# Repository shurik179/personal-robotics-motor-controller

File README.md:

# Personal Robotics Motor Controller

This repository contain design files for a 2-channel motor
controller board, designed by members of Personal Robotics discord server.

The controller is based on [DRV8874](https://www.ti.com/lit/ds/symlink/drv8874.pdf) motor driver ICs by TI. The  key
features of this controller are listed below:

* Support for 2 brushed DC motors, 5-24v

* Current limit per channel: 4.5A continuous (with heatsinks), current limited

* Overcurrent, undervoltage, and overtemperature protection

* Support for quadrature encoders for each motor (3.3v)

* An on-board MCU (RP2040) for reading encoder input and
  providing variety of close loop motor control modes

* Serial interface for control by a microcontroller or single board computer

This repository contains both board design files (as KiCad 6.0 project) and
firmware (written using Arduino IDE with Earl Philhower arduino-pico core for RP2040).

Detailed project information is available http://motor-controller.rtfd.io/

## Copyright

This project was started in 2021  by:

* Ichiro Furusato  (https://github.com/ifurusato)

* Adam Green (https://github.com/adamgreen/)

* shurik179 (https://github.com/shurik179)

It is released under Apache license; see file LICENSE for details.

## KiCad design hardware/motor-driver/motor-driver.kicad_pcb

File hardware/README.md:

# Hardware

This directory contains:

* Board design files (in KiCad 6.0 format)

* Bill of Materials (BOM)

The board specs are:

* Dimensions: 60x50 mm

* Stackup: 4-layer, 1.6mm thickness, 1oz copper thickness (outzide layers)

* Mounting holes: 4 holes for M3 screws, in the shape of rectangle 43x53mm

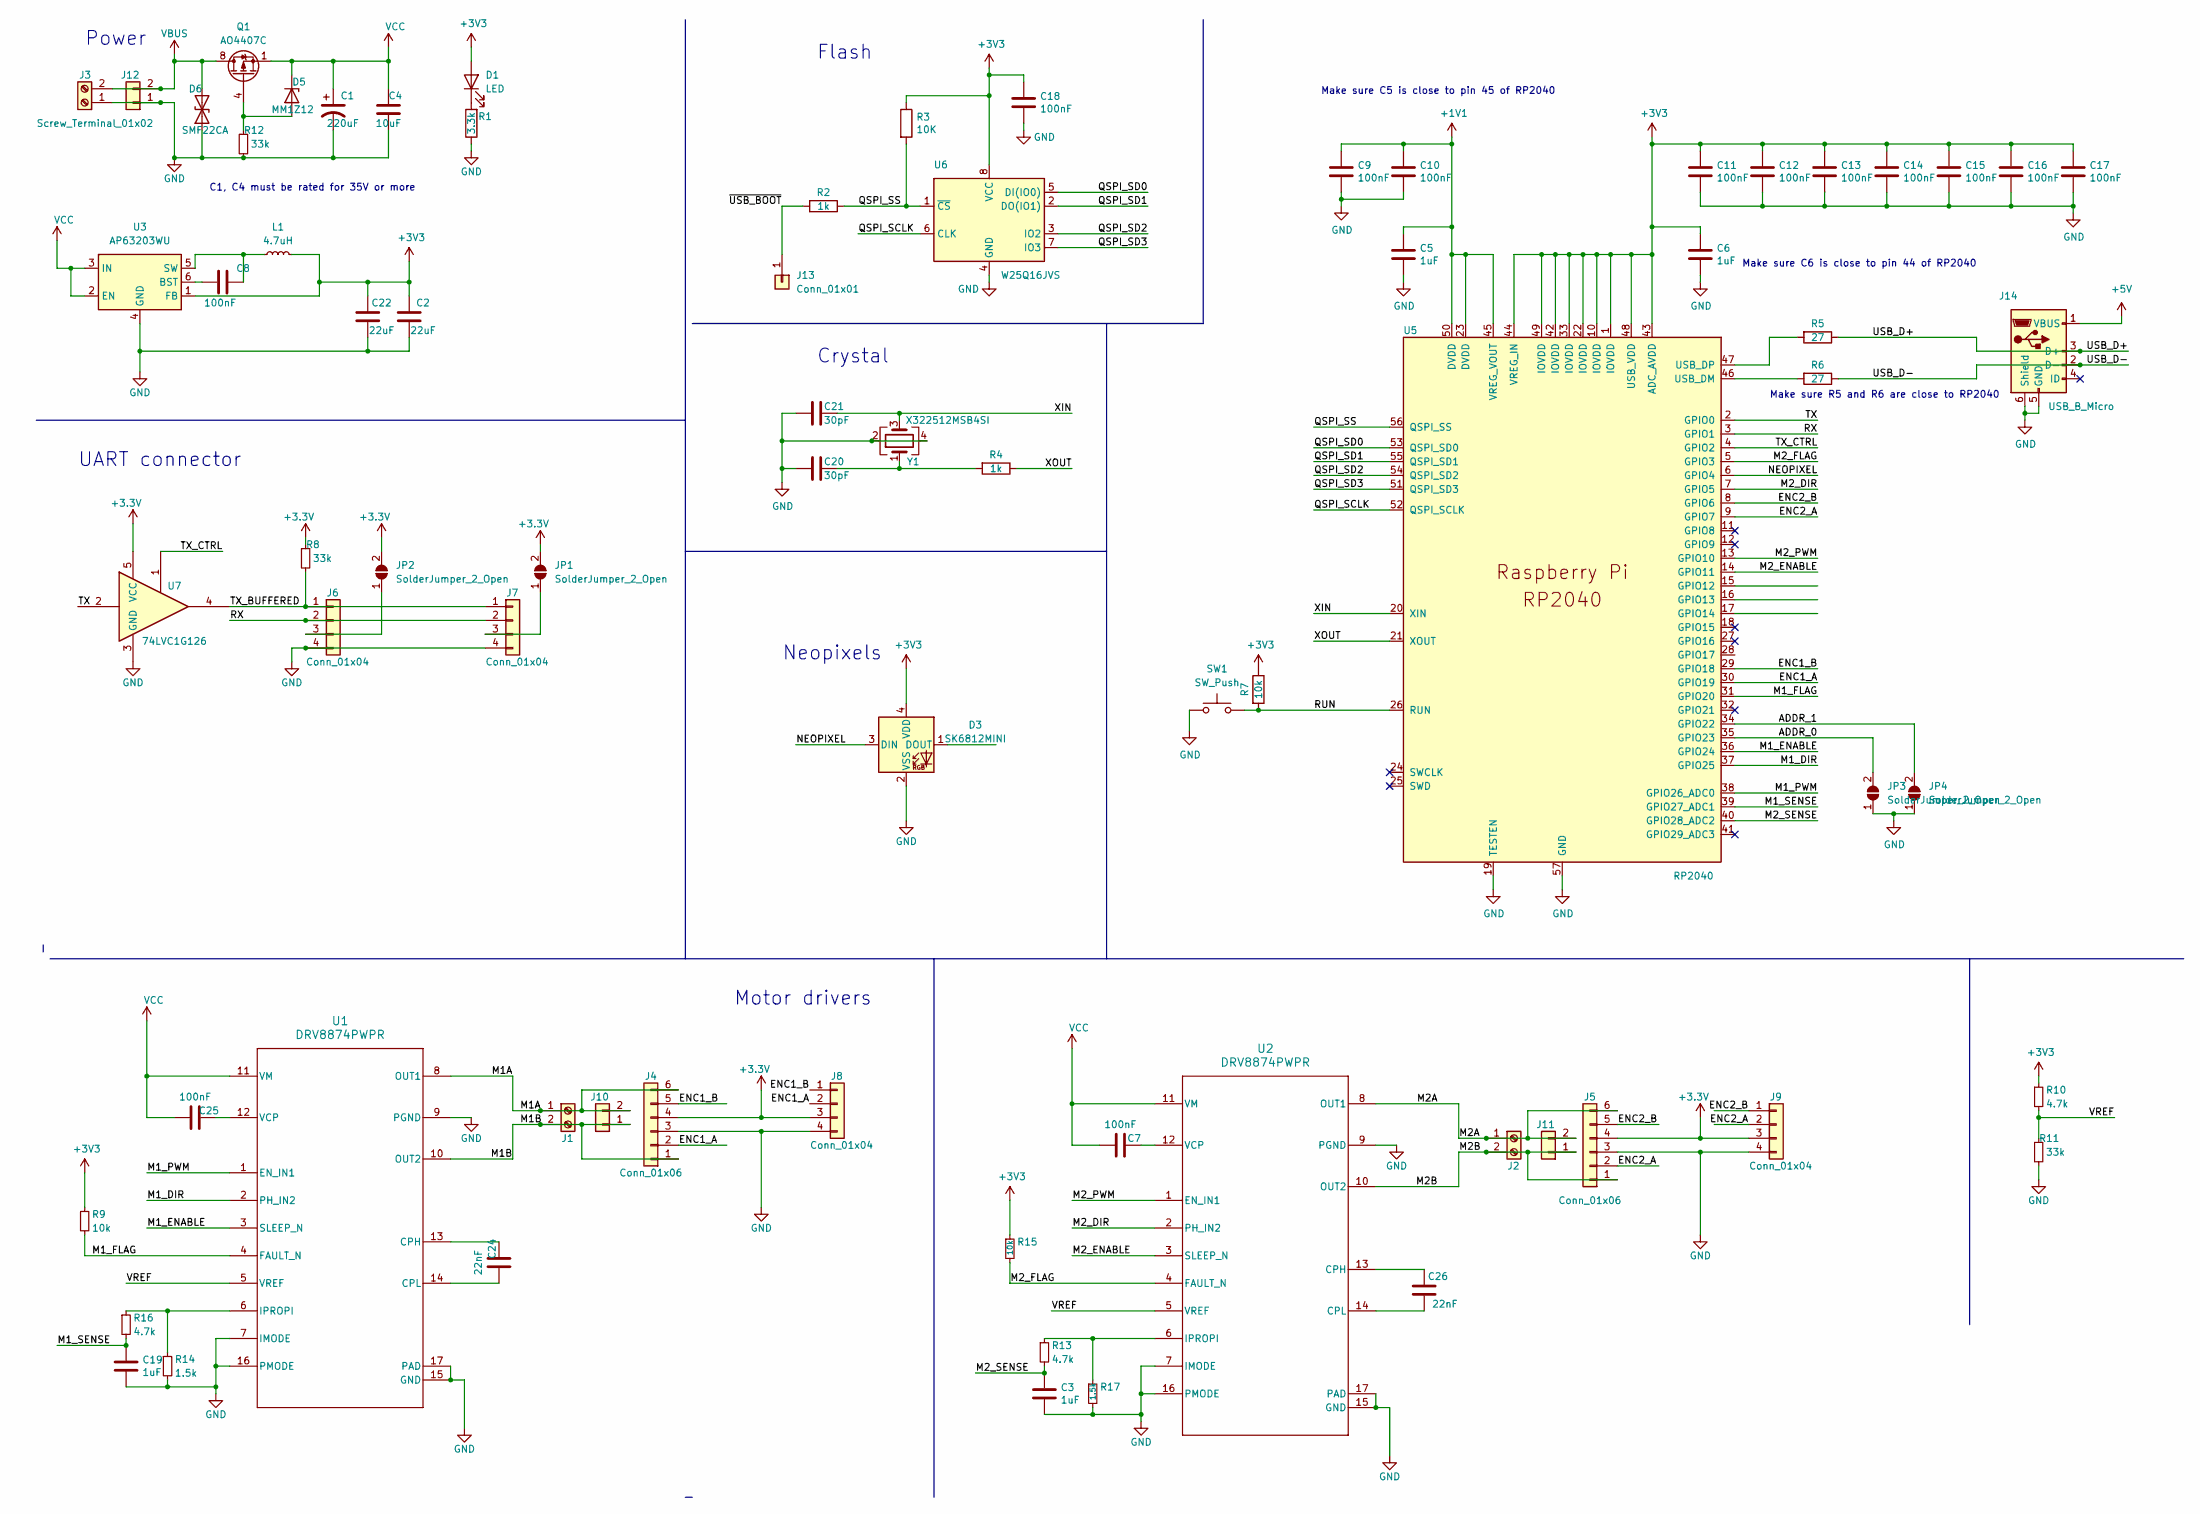
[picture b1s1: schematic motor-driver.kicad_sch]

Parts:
C1: 220uF; CP_Radial_D8.0mm_P3.50mm
C2, C22: 22uF; C_0805_2012Metric; LCSC C45783
C3, C5, C6, C19: 1uF; C_0402_1005Metric; LCSC C52923
C4: 10uF; C_1206_3216Metric; LCSC C13585
C7, C8, C9, C10, C11, C12, C13, C14, C15, C16, C17, C18, C25: 100nF; C_0402_1005Metric; LCSC C1525
C20, C21: 30pF; C_0402_1005Metric; LCSC C1570
C24, C26: 22nF; C_0402_1005Metric; LCSC C1532
D1: LED; LED_0805_2012Metric; LCSC C2297
D3: SK6812MINI; LED_SK6812MINI_PLCC4_3.5x3.5mm_P1.75mm; LCSC C2886570
D5: MM1Z12; D_SOD-123; LCSC C86234
D6: SMF22CA; D_SOD-123F; LCSC C353295
J1, J2, J3: Screw_Terminal_01x02; TerminalBlock_Phoenix_MKDS-1,5-2_1x02_P5.00mm_Horizontal_no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
J4, J5: Conn_01x06; PinHeader_1x06_P2.54mm_Vertical
J6, J7, J8, J9: Conn_01x04; JST_PH_B4B-PH-K_1x04_P2.00mm_Vertical
J10, J11: Conn_01x02; JST_VH_B2P-VH-B_1x02_P3.96mm_Vertical-nosilk
J12: Conn_01x02; AMASS_XT30UPB-M_1x02_P5.0mm_Vertical
J13: Conn_01x01; PinHeader_1x01_P2.54mm_Vertical
J14: USB_B_Micro; USB_Micro-B_Amphenol_10118194_Horizontal; LCSC C132563
JP1, JP2, JP3, JP4: SolderJumper_2_Open; SolderJumper-2_P1.3mm_Open_TrianglePad1.0x1.5mm
L1: 4.7uH; L_Sunlord_SWPA4018S; LCSC C60117
Q1: AO4407C; SOIC-8_3.9x4.9mm_P1.27mm; LCSC C469397
R1: 3.3k; R_0402_1005Metric; LCSC C25890
R2, R4: 1k; R_0402_1005Metric; LCSC C11702
R3: 10K; R_0402_1005Metric; LCSC C25744
R5, R6: 27; R_0402_1005Metric; LCSC C25100
R7, R9, R15: 10k; R_0402_1005Metric; LCSC C25744
R8, R11, R12: 33k; R_0402_1005Metric; LCSC C25779
R10, R13, R16: 4.7k; R_0402_1005Metric; LCSC C25900
R14, R17: 1.5k; R_0402_1005Metric; LCSC C25867
SW1: SW_Push; SW_SPST_PTS810; LCSC C116501
U1, U2: DRV8874PWPR; HTSSOP-16-1EP_4.4x5mm_P0.65mm_EP3.4x5mm_Mask2.46x3.55mm_The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; LCSC C1855818
U3: AP63203WU; TSOT-23-6; LCSC C780769
U5: RP2040; RP2040-QFN-56; LCSC C2040
U6: W25Q16JVS; SOIC-8_5.23x5.23mm_P1.27mm; LCSC C82317
U7: 74LVC1G126; SOT-23-5; LCSC C7834
Y1: X322512MSB4SI; Crystal_SMD_Abracon_ABM8G-4Pin_3.2x2.5mm; LCSC C9002

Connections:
+1V1: C5.1, C9.1, C10.1, U5.23 (DVDD), U5.45 (VREG_VOUT), U5.50 (DVDD)
+5V: J14.1 (VBUS)
/ADDR_0: JP3.2 (B), U5.35 (GPIO23)
/ADDR_1: JP4.2 (B), U5.34 (GPIO22)
/ENC1_A: J4.2, J8.2, U5.30 (GPIO19)
/ENC1_B: J4.5, J8.1, U5.29 (GPIO18)
/ENC2_A: J5.2, J9.2, U5.9 (GPIO7)
/ENC2_B: J5.5, J9.1, U5.8 (GPIO6)
/M1A: J1.1, J4.6, J10.2, U1.8 (OUT1)
/M1B: J1.2, J4.1, J10.1, U1.10 (OUT2)
/M1_DIR: U1.2 (PH_IN2), U5.37 (GPIO25)
/M1_ENABLE: U1.3 (SLEEP_N), U5.36 (GPIO24)
/M1_FLAG: R9.2, U1.4 (FAULT_N), U5.31 (GPIO20)
/M1_PWM: U1.1 (EN_IN1), U5.38 (GPIO26_ADC0)
/M1_SENSE: C19.1, R16.2, U5.39 (GPIO27_ADC1)
/M2A: J2.1, J5.6, J11.2, U2.8 (OUT1)
/M2B: J2.2, J5.1, J11.1, U2.10 (OUT2)
/M2_DIR: U2.2 (PH_IN2), U5.7 (GPIO5)
/M2_ENABLE: U2.3 (SLEEP_N), U5.14 (GPIO11)
/M2_FLAG: R15.2, U2.4 (FAULT_N), U5.5 (GPIO3)
/M2_PWM: U2.1 (EN_IN1), U5.13 (GPIO10)
/M2_SENSE: C3.1, R13.2, U5.40 (GPIO28_ADC2)
/NEOPIXEL: D3.3 (DIN), U5.6 (GPIO4)
/QSPI_SCLK: U5.52 (QSPI_SCLK), U6.6 (CLK)
/QSPI_SD0: U5.53 (QSPI_SD0), U6.5 (DI(IO0))
/QSPI_SD1: U5.55 (QSPI_SD1), U6.2 (DO(IO1))
/QSPI_SD2: U5.54 (QSPI_SD2), U6.3 (IO2)
/QSPI_SD3: U5.51 (QSPI_SD3), U6.7 (IO3)
/QSPI_SS: R2.1, R3.2, U5.56 (QSPI_SS), U6.1 (~CS)
/RUN: R7.2, SW1.2, U5.26 (RUN)
/RX: J6.2, J7.2, U5.3 (GPIO1)
/TX: U5.2 (GPIO0), U7.2
/TX_BUFFERED: J6.1, J7.1, R8.2, U7.4
/TX_CTRL: U5.4 (GPIO2), U7.1
/USB_D+: J14.3 (D+), R5.1
/USB_D-: J14.2 (D-), R6.1
/VREF: R10.2, R11.1, U1.5 (VREF), U2.5 (VREF)
/XIN: C21.1, U5.20 (XIN), Y1.3
/XOUT: R4.1, U5.21 (XOUT)
/~USB_BOOT: J13.1, R2.2
GND: C1.2, C2.1, C3.2, C4.1, C5.2, C6.2, C9.2, C10.2, C11.2, C12.2, C13.2, C14.2, C15.2, C16.2, C17.2, C18.2, C19.2, C20.2, C21.2, C22.1, D3.2 (VSS), D6.1 (A1), J3.1, J4.3, J5.3, J6.4, J7.4, J8.4, J9.4, J12.1, J14.5 (GND), J14.6 (Shield), JP3.1 (A), JP4.1 (A), R1.1, R11.2, R12.2, R14.2, R17.2, SW1.1, U1.7 (IMODE), U1.9 (PGND), U1.15 (GND), U1.16 (PMODE), U1.17 (PAD), U2.7 (IMODE), U2.9 (PGND), U2.15 (GND), U2.16 (PMODE), U2.17 (PAD), U3.4 (GND), U5.19 (TESTEN), U5.57 (GND), U6.4 (GND), U7.3 (GND), Y1.2, Y1.4
unnamed: C20.1, R4.2, Y1.1
unnamed: D1.1 (K), R1.2
unnamed: D5.2 (A), Q1.4 (G), R12.1
unnamed: J6.3, JP2.1 (A)
unnamed: J7.3, JP1.1 (A)
unnamed: C24.2, U1.13 (CPH)
unnamed: C24.1, U1.14 (CPL)
unnamed: R14.1, R16.1, U1.6 (IPROPI)
unnamed: C25.2, U1.12 (VCP)
unnamed: C26.2, U2.13 (CPH)
unnamed: C26.1, U2.14 (CPL)
unnamed: R13.1, R17.1, U2.6 (IPROPI)
unnamed: C7.2, U2.12 (VCP)
unnamed: C8.1, U3.6 (BST)
unnamed: C8.2, L1.1, U3.5 (SW)
unnamed: R6.2, U5.46 (USB_DM)
unnamed: R5.2, U5.47 (USB_DP)
VBUS: D6.2 (A2), J3.2, J12.2, Q1.5 (D), Q1.6 (D), Q1.7 (D), Q1.8 (D)
VCC: C1.1, C4.2, C7.1, C25.1, D5.1 (K), Q1.1 (S), Q1.2 (S), Q1.3 (S), U1.11 (VM), U2.11 (VM), U3.2 (EN), U3.3 (IN)

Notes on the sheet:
Make sure C5 is close to pin 45 of RP2040
Motor drivers
Crystal
C1, C4 must be rated for 35V or more
Neopixels
Make sure R5 and R6 are close to RP2040
Power
Make sure C6 is close to pin 44 of RP2040
Flash
UART connector

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
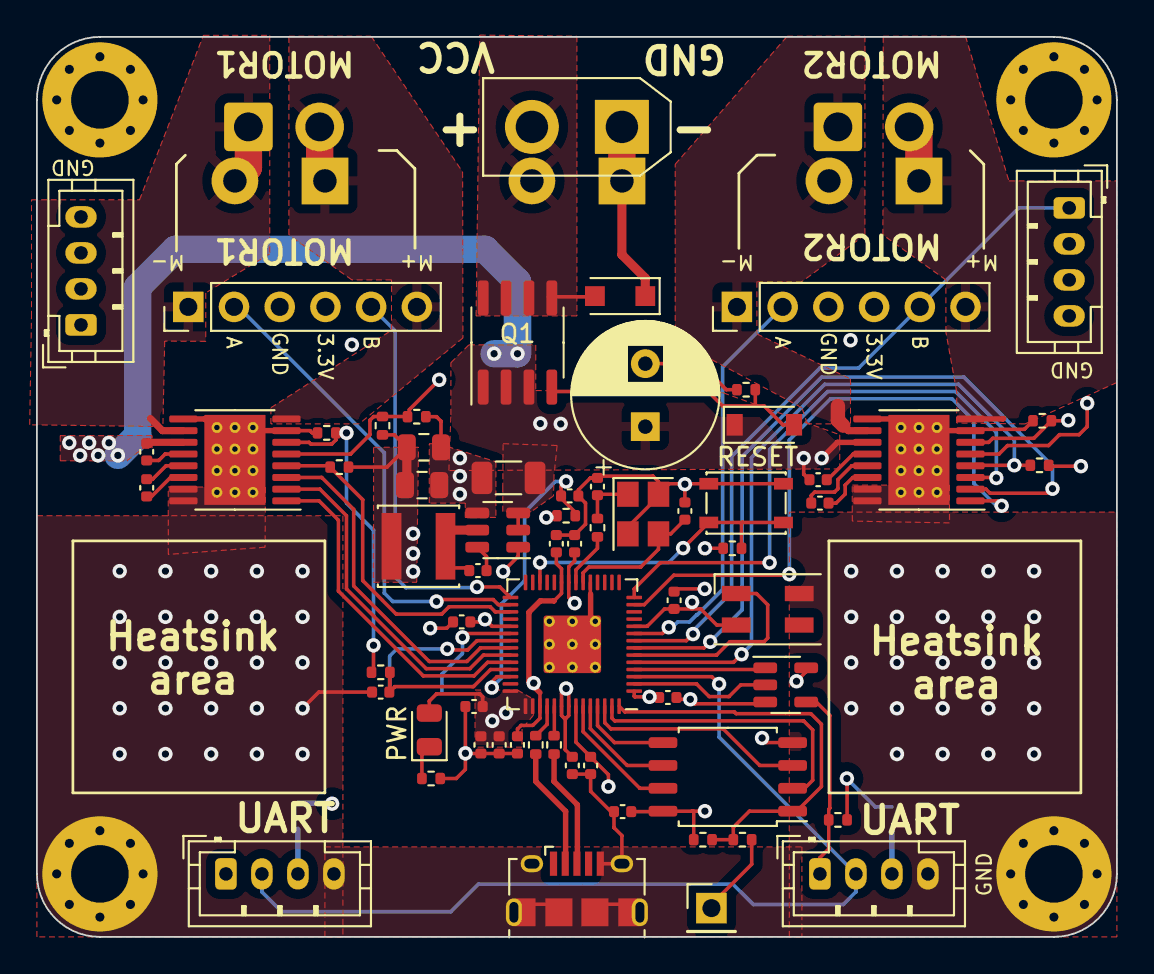
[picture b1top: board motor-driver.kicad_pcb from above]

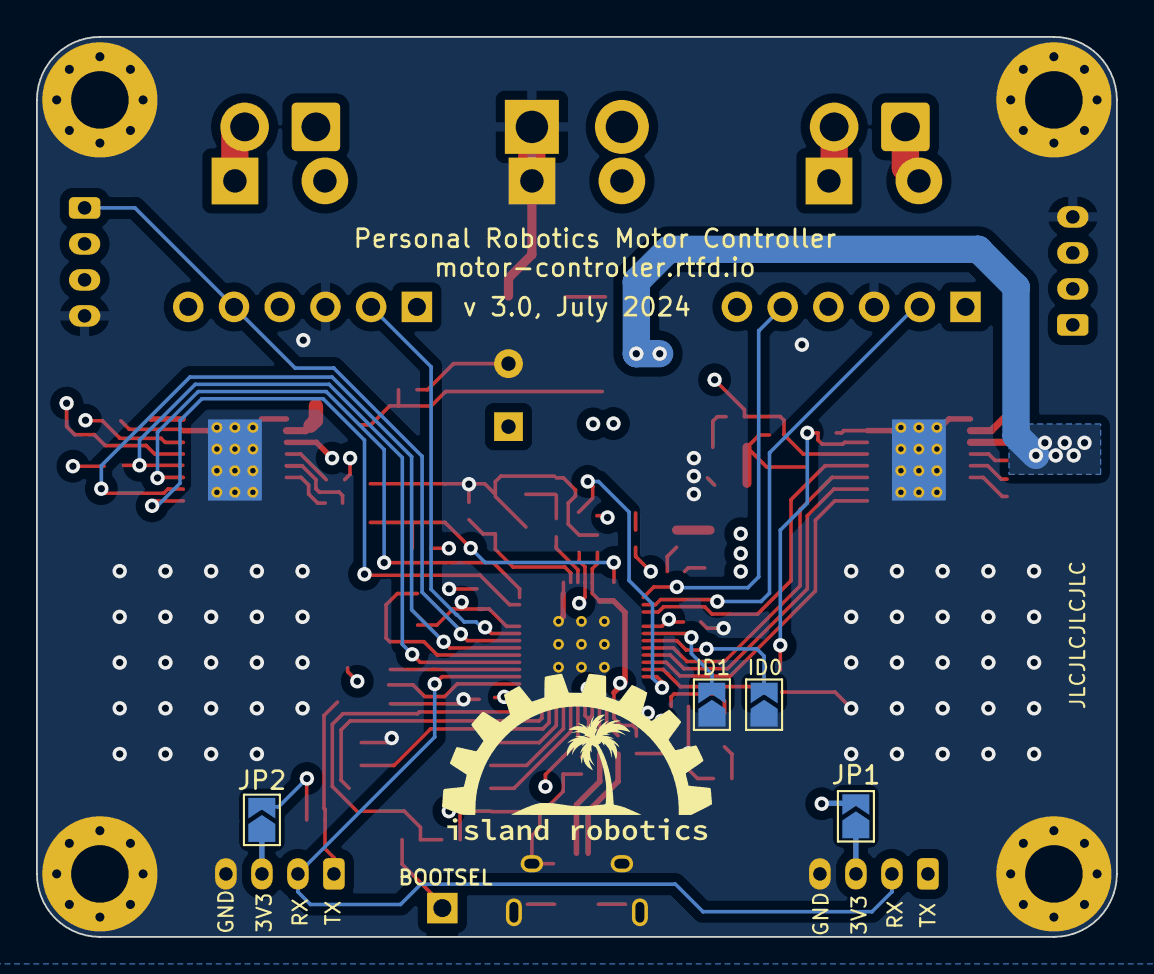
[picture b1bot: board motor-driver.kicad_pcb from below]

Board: 4 copper layers, 60.0 x 50.0 mm, 74 parts (4 on the bottom side), 60 nets.

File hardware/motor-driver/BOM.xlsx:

Component | Description | Part Number | References | Value | Footprint | Quantity Per PCB | Datasheet | LCSC | Comment
1 | AL electrolytic capacitor,220uF |  | C1, | 220uF | Radial_D8.0mm_P3.50mm | 1
2 | SMD capacitor, 10 uF, 16V |  | C2, C3, C22 | 10uF | 0805 | 3 |  | C15850
3 | SMD capacitor, 10 uF, 50V |  | C4, | 10uF | 1206 | 1 |  | C13585
4 | SMD capacitor |  | C5, C6, | 1uF | 0402 | 2 |  | C52923
5 | SMD capacitor |  | C7, C8, C9, C10, C11, C12, C13, C14, C15, C16, C17, C18, C23 | 100nF | 0402 | 13 |  | C1525
6 | SMD capacitor |  | C19 | 220nF | 0402 | 1 |  | C16772
7 | SMD capacitor |  | C20, C21, | 30pF | 0402 | 2 |  | C1570
8 | LED, green |  | D1, | LED | 0603 | 1 |  | C72043
9 | Schottky diode | B5819W | D2, |  | SOD123 | 1 |  | C8598
10 | RGB LED with integrated controller | WS2812B-mini | D3, D4, |  | 3535 | 2 |  | C527089
11 | JST SH 4p connector, horizontal | A1002WR-S-4P | J6, J7 |  |  | 2 |  | C239522
12 | USB Micro Type B connector | 10118194-0001LF | J14, |  |  | 1 |  | C132563
13 | Inductor, 10uH, 1A | SWPA4012S100 | L1, | 10uH | Inductor 4.0x4.0mm | 1 |  | C36405
14 | P-Channel Power MOSFET, SO-8 | AO4407C | Q1, | AO4407C | SOIC8 | 1 |  | C469397
15 | SMD resistor, 3.3k, 0402 |  | R1, | 3.3k | 0402 | 1 |  | C25890
16 | SMD resistor, 1k, 0402 |  | R2, R4, | 1k | 0402 | 2 |  | C11702
17 | SMD resistor, 10k, 0402 |  | R3, R7,R8,R9,R10 | 10k | 0402 | 5 |  | C25744
18 | SMD resistor, 27R, 0402 |  | R5, R6, | 27R | 0402 | 2 |  | C25100
19 | SMD resistor, 54.9k, 0402 |  | R11, | 54.9k | 0402 | 1 |  | C11626
20 | Push button switch, generic, two pins | PTS810SJM250 | SW1, | PTS810SJM250 | 3.2x4.2mm | 1 |  | C116501
21 | Brushed DC Motor Driver, PWM Control, 45V, 3.6A, Current limiting, HTSOP-8 | TLE9201SG | U1, U2, | TLE9201SG | SO-12 | 2 |  | C2653438
22 | 600mA 42V Input Step-Down DC-DC Regulator, Adjustable Output Voltage, 550kHz, T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 | LV2842XLVDDCR | U3, | LM2842X | SOT-23-6 | 1 |  | C225807
23 | 300mA low dropout linear regulator, shutdown pin, 2.5V-6V input voltage, 3.3V f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 | AP2120N-3.3 | U4, | AP2120N-3.3 | SOT-23-3 | 1 |  | C155508
24 | RP2040 32bit MCU | RP2040 | U5, | RP2040 | QFN-56 | 1 |  | C2040
25 | 16Mb Serial Flash Memory, Standard/Dual/Quad SPI, SOIC-8 | W25Q16JVSSIQ | U6, | W25Q16JVSSIQ | SOIC8-208mil | 1 |  | C82317
26 | Four pin crystal, GND on pins 2 and 4 | Crystal_GND24 | Y1, | X322512MSB4SI | 3.2x2.5mm | 1 |  | C9002

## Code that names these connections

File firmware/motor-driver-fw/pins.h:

#ifndef _MD_PINS_H
#define _MD_PINS_H


//pins
#define PIN_MD_SDA       0
#define PIN_MD_SCL       1
#define PIN_MOTOR1_DIR   27
#define PIN_MOTOR1_PWM   28
#define PIN_MOTOR2_DIR   2
#define PIN_MOTOR2_PWM   3
#define PIN_JMP1         5
#define PIN_JMP2         4
#define PIN_ENC1_A       16
#define PIN_ENC1_B       15
#define PIN_ENC2_A       14
#define PIN_ENC2_B       13
#define PIN_NEOPIXEL     18
#define PIN_ERROR1       17
#define PIN_ERROR2       12
#define PIN_DISABLE      26

//function declaration to initialize pins
void pins_init();
#endif

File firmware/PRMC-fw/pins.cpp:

#include <Arduino.h>
#include "pins.h"

void pins_init(){
  pinMode(PIN_TX_CTRL, OUTPUT);
  pinMode(PIN_ERROR1, INPUT);
  pinMode(PIN_ERROR2, INPUT);
  pinMode(PIN_ADDR0, INPUT_PULLUP);
  pinMode(PIN_ADDR1, INPUT_PULLUP);
  pinMode(PIN_ENABLE1, OUTPUT);
  pinMode(PIN_ENABLE2, OUTPUT);
  pinMode(PIN_MOTOR1_DIR, OUTPUT);
  pinMode(PIN_MOTOR1_PWM, OUTPUT);
  pinMode(PIN_MOTOR2_DIR, OUTPUT);
  pinMode(PIN_MOTOR2_PWM, OUTPUT);
  pinMode(PIN_NEOPIXEL, OUTPUT);
  //pinMode(PIN_M1_SENSE, INPUT);
  //pinMode(PIN_M2_SENSE, INPUT);
  analogReadResolution(12); //set ADC resolution to 12 bits
}

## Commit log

2021-12-11 initial upload
2021-12-13 firmware updates
2021-12-14 fw update - basic functionality complete
2021-12-19 first attempt at user micropython library
2021-12-20 temporary fix of error reporting
2021-12-21 now with encoder support
2021-12-21 Changing license to Apache
2021-12-25 fixing i2c issues; changed frequency
2021-12-25 started user docs
2021-12-27 fixing register map, so I don't write int32 into 2 bytes
2021-12-28 added PID mode
2021-12-28 docs update
2021-12-28 fixing firmware version number init
2021-12-29 docs: adding register map
2021-12-29 testing csv includes
2021-12-31 added schematics
2021-12-31 renamed firmware directory
2021-12-31 updating for new name - PRMC
2021-12-31 renaming
2022-01-01 minor docs fixes
2022-01-02 updated board design files for KiCad 6.0
2022-02-15 Initial commit for version 2
2022-02-15 docs update for v2
2022-02-15 typo fix
2022-04-12 new images for docs
2022-04-12 neopixel fix
2022-04-14 Renaming to PRMC. Fixing enable in firmware
2022-04-14 minor docs update
2022-04-21 changing motor range to -1.0...1.0
2022-04-21 fixing copyright year
2022-04-22 change how we check status in firmware
2022-04-22 added tindie link
2022-04-22 change current limit to 4.5A
2024-07-02 starting work on v3
2024-07-02 Readme update
2024-07-02 version 3.0.0-beta1
2024-07-26 July update
